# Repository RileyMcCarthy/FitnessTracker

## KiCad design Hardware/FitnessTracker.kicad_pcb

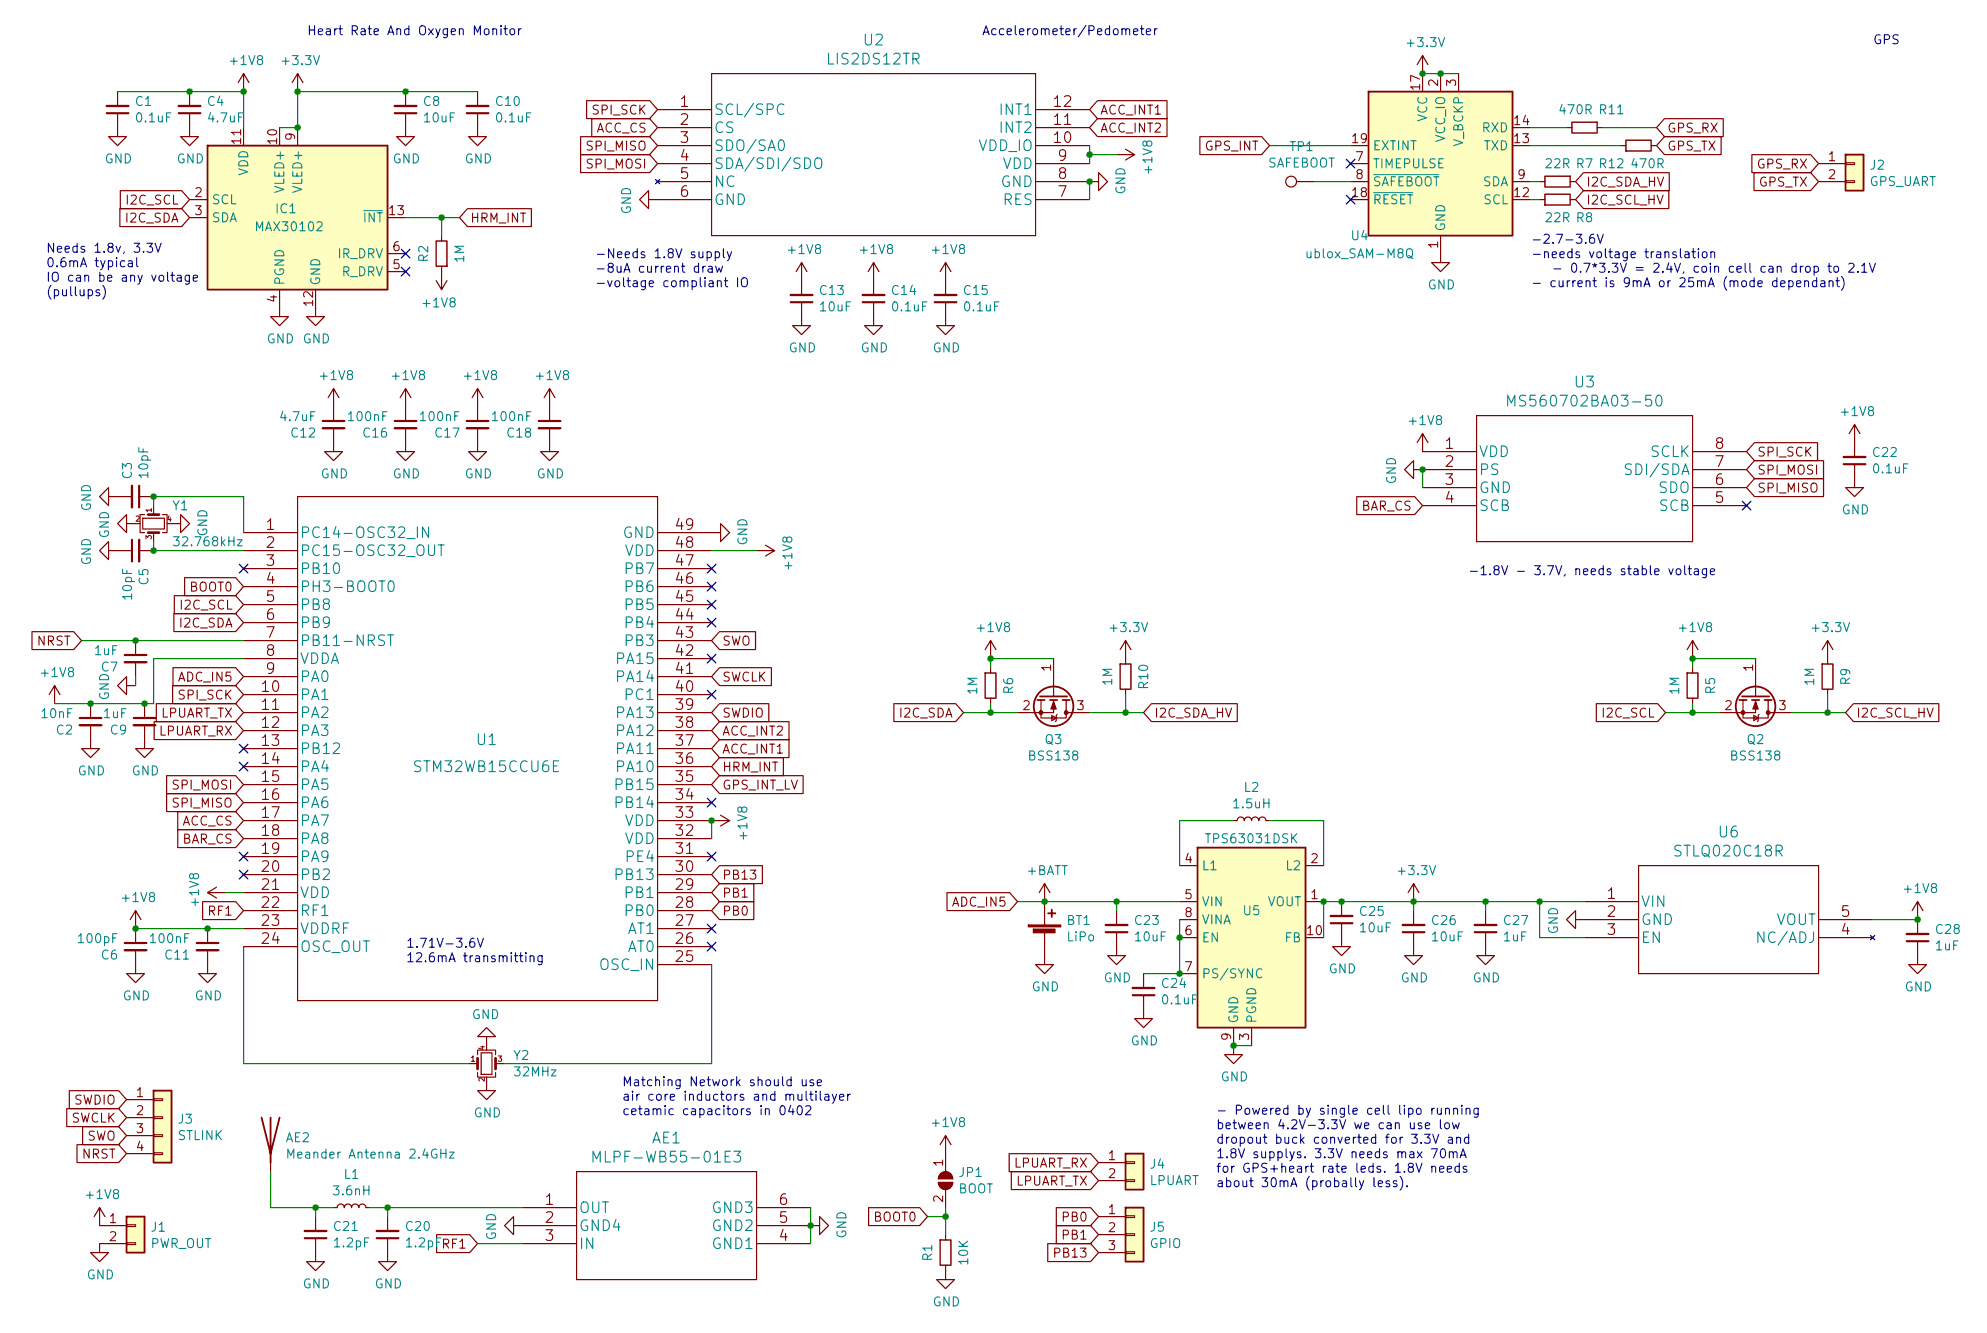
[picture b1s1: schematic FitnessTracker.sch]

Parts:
AE1: MLPF-WB55-01E3; DIGIKEY ‎497-19088-1-ND‎
AE2: Meander Antenna 2.4GHz; 2.4GHz Antenna; DIGIKEY NA
BT1: LiPo; PinHeader_1x02_P2.54mm_Vertical; DIGIKEY NA
C1, C10, C14, C15, C22, C24: 0.1uF; C_0402_1005Metric; DIGIKEY NA
C2: 10nF; C_0402_1005Metric; DIGIKEY NA
C3, C5: 10pF; C_0402_1005Metric; DIGIKEY NA
C4, C12: 4.7uF; C_0402_1005Metric; DIGIKEY NA
C6: 100pF; C_0402_1005Metric; DIGIKEY NA
C7, C9, C27, C28: 1uF; C_0402_1005Metric; DIGIKEY NA
C8, C13, C23, C25, C26: 10uF; C_0402_1005Metric; DIGIKEY NA
C11, C16, C17, C18: 100nF; C_0402_1005Metric; DIGIKEY NA
C20, C21: 1.2pF; C_0402_1005Metric; DIGIKEY NA
IC1: MAX30102; Maxim_OLGA-14_3.3x5.6mm_P0.8mm; DIGIKEY MAX30102EFD+-ND
J1: PWR_OUT; PinHeader_1x02_P1.00mm_Vertical; DIGIKEY NA
J2: GPS_UART; PinHeader_1x02_P1.00mm_Vertical; DIGIKEY NA
J3: STLINK; PinHeader_1x04_P1.00mm_Vertical; DIGIKEY NA
J4: LPUART; PinHeader_1x02_P1.00mm_Vertical; DIGIKEY NA
J5: GPIO; PinHeader_1x03_P1.00mm_Vertical; DIGIKEY NA
JP1: BOOT; SolderJumper-2_P1.3mm_Open_Pad1.0x1.5mm; DIGIKEY NA
L1: 3.6nH; L_0402_1005Metric; DIGIKEY 490-6571-1-ND
L2: 1.5uH; L_0402_1005Metric
Q2, Q3: BSS138; SOT-323_SC-70; DIGIKEY BSS138W-FDITR-ND
R1: 10K; R_0402_1005Metric; DIGIKEY CRGCQ0402J10K‎
R2, R5, R6, R9, R10: 1M; R_0402_1005Metric; DIGIKEY 2037-PFR05S-105-FNHTR-ND
R7, R8: 22R; R_0402_1005Metric; DIGIKEY 10-ERJ-U02J220XTR-ND
R11, R12: 470R; R_0402_1005Metric; DIGIKEY 2019-RK73B1ETTP471JTR-ND
TP1: SAFEBOOT; TestPoint_Pad_1.0x1.0mm; DIGIKEY NA
U1: STM32WB15CCU6E; DIGIKEY STM32WB15CCU6E‎
U2: LIS2DS12TR; DIGIKEY 497-16261-2-ND
U3: MS560702BA03-50; DIGIKEY 223-1198-2-ND
U4: ublox_SAM-M8Q; DIGIKEY SAM-M8Q-0-10‎
U5: TPS63031DSK; WSON-10-1EP_2.5x2.5mm_P0.5mm_EP1.2x2mm
U6: STLQ020C18R; DIGIKEY STLQ020C18R‎
Y1: 32.768kHz; 8Q20000MAAVT
Y2: 32MHz; 8Q20000MAAVT; DIGIKEY 887-8Q-32.000MEIE-TTR-ND

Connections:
+1V8: C1.2, C2.1, C4.2, C6.1, C9.1, C11.1, C12.1, C13.2, C14.2, C15.2, C16.1, C17.1, C18.1, C22.2, C28.2, IC1.11 (VDD), J1.1, JP1.1 (A), Q2.1 (G), Q3.1 (G), R2.1, R5.1, R6.1, U1.8 (VDDA), U1.21 (VDD), U1.23 (VDDRF), U1.32 (VDD), U1.33 (VDD), U1.48 (VDD), U2.9 (VDD), U2.10 (VDD_IO), U3.1 (VDD), U6.5 (VOUT)
+3V3: C8.2, C10.2, C25.2, C26.2, C27.2, IC1.9 (VLED+), IC1.10 (VLED+), R9.1, R10.1, U4.2 (VCC_IO), U4.3 (V_BCKP), U4.17 (VCC), U5.1 (VOUT), U5.10 (FB), U6.1 (VIN), U6.3 (EN)
ACC_CS: U1.17 (PA7), U2.2 (CS)
ACC_INT1: U1.37 (PA11), U2.12 (INT1)
ACC_INT2: U1.38 (PA12), U2.11 (INT2)
ADC_IN5: BT1.1 (+), C23.2, U1.9 (PA0), U5.5 (VIN)
BAR_CS: U1.18 (PA8), U3.4 (SCB)
BOOT0: JP1.2 (B), R1.1, U1.4 (PH3-BOOT0)
GND: AE1.2 (GND4), AE1.4 (GND1), AE1.5 (GND2), AE1.6 (GND3), BT1.2 (-), C1.1, C2.2, C3.2, C4.1, C5.1, C6.2, C7.2, C8.1, C9.2, C10.1, C11.2, C12.2, C13.1, C14.1, C15.1, C16.2, C17.2, C18.2, C20.1, C21.1, C22.1, C23.1, C24.1, C25.1, C26.1, C27.1, C28.1, IC1.4 (PGND), IC1.12 (GND), J1.2, R1.2, U1.49 (GND), U2.6 (GND), U2.7 (RES), U2.8 (GND), U3.2 (PS), U3.3 (GND), U4.1 (GND), U4.4 (GND), U4.5 (GND), U4.6 (GND), U4.10 (GND), U4.11 (GND), U4.15 (GND), U4.16 (GND), U4.20 (GND), U5.3 (PGND), U5.9 (GND), U5.11 (PGND), U6.2 (GND), Y1.2, Y1.4, Y2.2, Y2.4
GPS_INT: U4.19 (EXTINT)
GPS_INT_LV: U1.35 (PB15)
GPS_RX: J2.1, R11.1
GPS_TX: J2.2, R12.2
HRM_INT: IC1.13 (~INT), R2.2, U1.36 (PA10)
I2C_SCL: IC1.2 (SCL), Q2.2 (S), R5.2, U1.5 (PB8)
I2C_SCL_HV: Q2.3 (D), R8.2, R9.2
I2C_SDA: IC1.3 (SDA), Q3.2 (S), R6.2, U1.6 (PB9)
I2C_SDA_HV: Q3.3 (D), R7.1, R10.2
LPUART_RX: J4.1, U1.12 (PA3)
LPUART_TX: J4.2, U1.11 (PA2)
NRST: C7.1, J3.4, U1.7 (PB11-NRST)
unnamed: AE1.1 (OUT), C20.2, L1.2
unnamed: AE2.1, C21.2, L1.1
unnamed: C3.1, U1.1 (PC14-OSC32_IN), Y1.1
unnamed: C5.2, U1.2 (PC15-OSC32_OUT), Y1.3
unnamed: C24.2, U5.6 (EN), U5.7 (PS/SYNC), U5.8 (VINA)
unnamed: L2.1, U5.4 (L1)
unnamed: L2.2, U5.2 (L2)
unnamed: R7.2, U4.9 (SDA)
unnamed: R8.1, U4.12 (SCL)
unnamed: R11.2, U4.14 (RXD)
unnamed: R12.1, U4.13 (TXD)
unnamed: TP1.1, U4.8 (~SAFEBOOT)
unnamed: U1.24 (OSC_OUT), Y2.1
unnamed: U1.25 (OSC_IN), Y2.3
PB0: J5.1, U1.28 (PB0)
PB1: J5.2, U1.29 (PB1)
PB13: J5.3, U1.30 (PB13)
RF1: AE1.3 (IN), U1.22 (RF1)
SPI_MISO: U1.16 (PA6), U2.3 (SDO/SA0), U3.6 (SDO)
SPI_MOSI: U1.15 (PA5), U2.4 (SDA/SDI/SDO), U3.7 (SDI/SDA)
SPI_SCK: U1.10 (PA1), U2.1 (SCL/SPC), U3.8 (SCLK)
SWCLK: J3.2, U1.41 (PA14)
SWDIO: J3.1, U1.39 (PA13)
SWO: J3.3, U1.43 (PB3)

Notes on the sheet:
Matching Network should use air core inductors and multilayer cetamic capacitors in 0402
1.71V-3.6V 12.6mA transmitting
Needs 1.8v, 3.3V 0.6mA typical IO can be any voltage (pullups)
-Needs 1.8V supply -8uA current draw -voltage compliant IO
-2.7-3.6V -needs voltage translation - 0.7*3.3V = 2.4V, coin cell can drop to 2.1V - current is 9mA or 25mA (mode dependant)
-1.8V - 3.7V, needs stable voltage
- Powered by single cell lipo running between 4.2V-3.3V we can use low dropout buck converted for 3.3V and 1.8V supplys. 3.3V needs max 70mA for GPS+heart rate leds. 1.8V needs about 30mA (probally less).
Heart Rate And Oxygen Monitor
Accelerometer/Pedometer
GPS

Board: 4 copper layers, 60 parts (8 on the bottom side), 43 nets, no tracks yet.

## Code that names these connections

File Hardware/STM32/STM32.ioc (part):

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Mcu.Name=STM32WB15CCUxE
Mcu.Package=UFQFPN48
Mcu.UserName=STM32WB15CCUxE
PA0.Signal=ADCx_IN5
PA1.Mode=Full_Duplex_Master
PA1.Signal=SPI1_SCK
PA10.GPIOParameters=GPIO_Label
PA10.GPIO_Label=HRM_INT
PA10.Signal=GPIO_Input
PA11.GPIOParameters=GPIO_Label
PA11.GPIO_Label=ACC_INT1
PA11.Signal=GPIO_Input
PA12.GPIOParameters=GPIO_Label
PA12.GPIO_Label=ACC_INT2
PA12.Signal=GPIO_Input
PA13.Mode=Trace_Asynchronous_SW
PA13.Signal=SYS_JTMS-SWDIO
PA14.Mode=Trace_Asynchronous_SW
PA14.Signal=SYS_JTCK-SWCLK
PA2.Mode=Asynchronous
PA2.Signal=LPUART1_TX
PA3.Mode=Asynchronous
PA3.Signal=LPUART1_RX
PA6.Mode=Full_Duplex_Master
PA6.Signal=SPI1_MISO
PA7.GPIOParameters=GPIO_Label
PA7.GPIO_Label=ACC_CS
PA7.Signal=GPIO_Output
PA8.GPIOParameters=GPIO_Label
PA8.GPIO_Label=BAR_CS
PA8.Signal=GPIO_Output
PB0.Signal=GPIO_Input
PB1.Signal=GPIO_Input
PB15.GPIOParameters=GPIO_Label
PB15.GPIO_Label=GPS_INT
PB15.Signal=GPIO_Input
PB3.Mode=Trace_Asynchronous_SW
PB3.Signal=SYS_JTDO-SWO
PB5.Mode=Full_Duplex_Master
PB5.Signal=SPI1_MOSI
PB8.Mode=I2C
PB8.Signal=I2C1_SCL
PB9.Mode=I2C
PB9.Signal=I2C1_SDA
PC14-OSC32_IN.Mode=LSE-External-Oscillator
PC14-OSC32_IN.Signal=RCC_OSC32_IN
PC15-OSC32_OUT.Mode=LSE-External-Oscillator
PC15-OSC32_OUT.Signal=RCC_OSC32_OUT
RCC.HSE_VALUE=32000000
RCC.SYSCLKFreq_VALUE=32000000
board=custom

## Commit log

2021-07-15 init commit
2021-07-17 schematic complete, begining pcb layout process
2021-07-20 completed rough layout of pcb

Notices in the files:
parts and their libraries:
Copyright 2021 Accelerated Designs. All rights reserved.
